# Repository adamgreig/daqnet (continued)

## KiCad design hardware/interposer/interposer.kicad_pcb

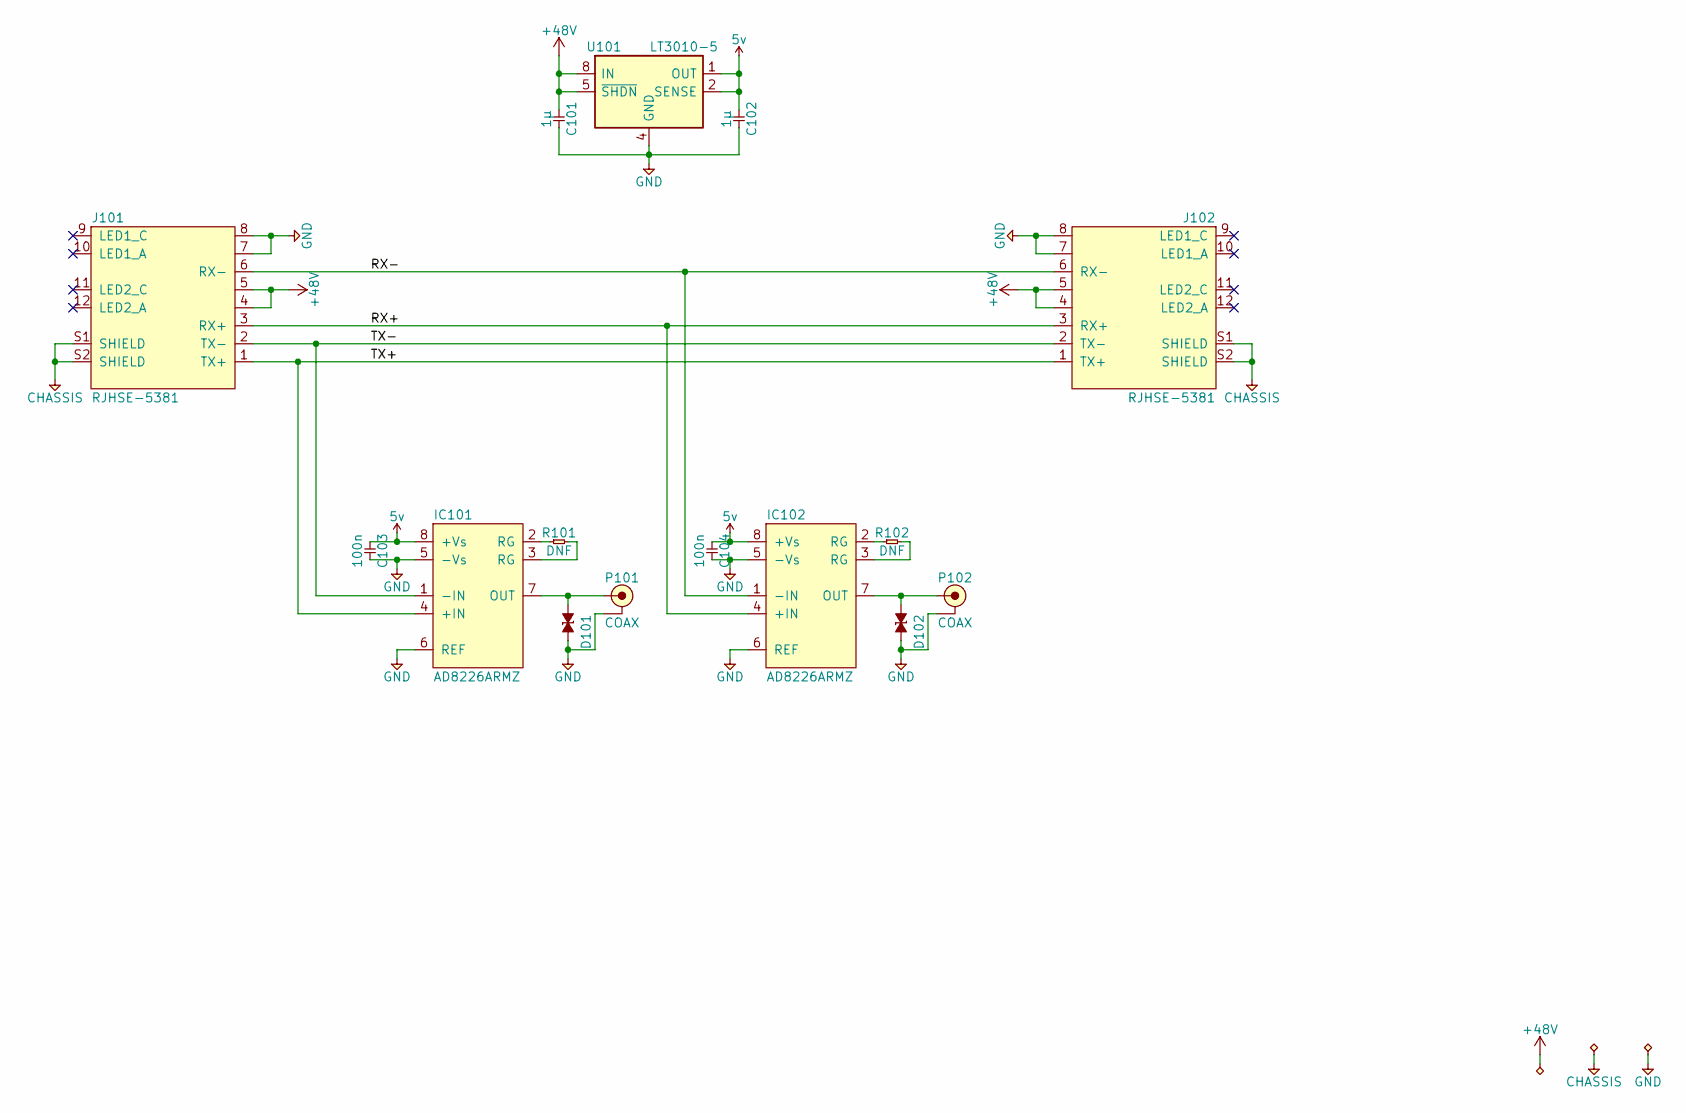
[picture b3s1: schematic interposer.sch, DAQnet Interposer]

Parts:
C101, C102: 1µ; 0805
C103, C104: 100n; 0402
D101: ESD_DIODE; 0402
D102: ESD_DIODE; 0402; Farnell 2368169
IC101, IC102: AD8226ARMZ; MSOP-8
J101, J102: RJHSE-5381; RJHSE-538X
P101, P102: COAX; SMA-EDGE
R101, R102: DNF; 0402
U101: LT3010-5; MSOP-8-1EP_3x3mm_P0.65mm_EP1.68x1.88mm

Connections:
5v: C102.1, C103.1, C104.1, IC101.8 (+Vs), IC102.8 (+Vs), U101.1 (OUT), U101.2 (SENSE)
+48V: C101.1, J101.4, J101.5, J102.4, J102.5, U101.5 (~SHDN), U101.8 (IN)
/RX+: IC102.4 (+IN), J101.3 (RX+), J102.3 (RX+)
/RX-: IC102.1 (-IN), J101.6 (RX-), J102.6 (RX-)
/TX+: IC101.4 (+IN), J101.1 (TX+), J102.1 (TX+)
/TX-: IC101.1 (-IN), J101.2 (TX-), J102.2 (TX-)
CHASSIS: J101.S1 (SHIELD), J101.S2 (SHIELD), J102.S1 (SHIELD), J102.S2 (SHIELD)
GND: C101.2, C102.2, C103.2, C104.2, D101.2, D102.2, IC101.5 (-Vs), IC101.6 (REF), IC102.5 (-Vs), IC102.6 (REF), J101.7, J101.8, J102.7, J102.8, P101.2 (GND), P102.2 (GND), U101.4 (GND), U101.9 (GND)
unnamed: D101.1, IC101.7 (OUT), P101.1 (RF)
unnamed: D102.1, IC102.7 (OUT), P102.1 (RF)
unnamed: IC101.2 (RG), R101.1
unnamed: IC101.3 (RG), R101.2
unnamed: IC102.2 (RG), R102.1
unnamed: IC102.3 (RG), R102.2

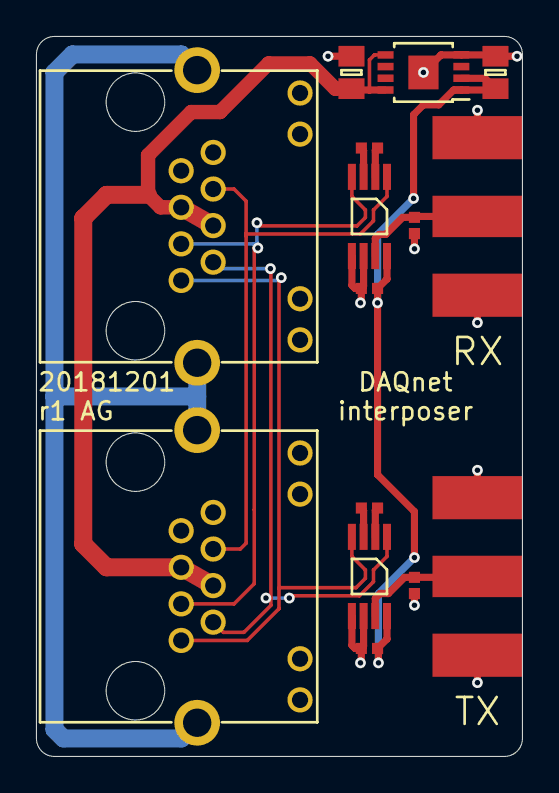
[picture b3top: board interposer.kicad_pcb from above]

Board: 2 copper layers, 27.0 x 40.0 mm, 15 parts (0 on the bottom side), 14 nets.

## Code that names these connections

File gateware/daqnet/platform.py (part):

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        ),
        Resource(
            "daqnet", 0,
            Subsignal("led1", Pins("A3", dir="o")),
            Subsignal("led2", Pins("A4", dir="o")),
            Subsignal("txp", Pins("C2", dir="o")),
            Subsignal("txn", Pins("C1", dir="o")),
            Subsignal("rx", Pins("B2", dir="i")),
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            "rmii", 0,
            Subsignal("txd0", Pins("J3", dir="o")),
            Subsignal("txd1", Pins("L1", dir="o")),
            Subsignal("txen", Pins("L2", dir="o")),
            Subsignal("rxd0", Pins("K5", dir="i")),
            Subsignal("rxd1", Pins("J5", dir="i")),
            Subsignal("crs_dv", Pins("L4", dir="i")),
            Subsignal("ref_clk", Pins("K4", dir="i")),
        ),
        Resource(
            "mdio", 0,
            Subsignal("mdc", Pins("K3", dir="o")),
            Subsignal("mdio", Pins("L3", dir="io")),
        ),
        Resource(
            "phy", 0,
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        ),
        Resource(
            "daqnet", 0,
            Subsignal("led1", Pins("C4", dir="o")),
            Subsignal("led2", Pins("D3", dir="o")),
            Subsignal("txp", Pins("B1", dir="o")),
            Subsignal("txn", Pins("B2", dir="o")),
            Subsignal("rx", Pins("C1", dir="i")),
        ),
        Resource(
            "daqnet", 1,
            Subsignal("led1", Pins("D2", dir="o")),
            Subsignal("led2", Pins("C3", dir="o")),
            Subsignal("txp", Pins("E1", dir="o")),
            Subsignal("txn", Pins("D1", dir="o")),
            Subsignal("rx", Pins("E3", dir="i")),
        ),
        Resource(
            "daqnet", 2,
            Subsignal("led1", Pins("G3", dir="o")),
            Subsignal("led2", Pins("F3", dir="o")),
            Subsignal("txp", Pins("F1", dir="o")),
            Subsignal("txn", Pins("F2", dir="o")),
            Subsignal("rx", Pins("G2", dir="i")),
        ),
        Resource(
            "daqnet", 3,
            Subsignal("led1", Pins("F4", dir="o")),
            Subsignal("led2", Pins("H3", dir="o")),
            Subsignal("txp", Pins("H1", dir="o")),
            Subsignal("txn", Pins("H2", dir="o")),
            Subsignal("rx", Pins("K1", dir="i")),
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
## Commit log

2018-11-26 initial commit. some pcb work and generic gateware.
2018-11-27 rtm proto sensor and switch
2018-11-27 rename to daqnet
2018-11-27 add protoswitch/sensor platforms
2018-11-29 fix annotations on switch; generate BOMs
2018-11-29 remove backup files
2018-12-01 add interposer
2018-12-03 add interposer bom
2018-12-03 add mdio controller
2018-12-03 add write test; randomise tests; swap rise/fall logic into clock generation; replace array with shifts
2018-12-03 swap back to using arrays as they use fewer resources
2018-12-03 rename register to reg_addr
2018-12-03 tidy up mdio
2018-12-04 Add start of MAC and add PHY controller
2018-12-05 Fix MDIO and MAC link detection
2018-12-05 tidy up mac/mdio
2018-12-06 Add first go at CRC32. Could perhaps get double throughput and need to check exactly what bit and byte order ethernet FCS really is.
2018-12-08 RMII RX working (mostly?)
2018-12-08 Reset CRC module each frame
2018-12-09 Improve RMII CDC
2018-12-09 Add MAC address matching to MAC
2018-12-10 Improve LED function
2018-12-10 Refactor mac address matching out of rmii
2018-12-10 RMII TX
2018-12-10 Add TX to MAC; add IPG to TX; demo spamming TX
2018-12-11 Working MAC TX/RX
2018-12-20 Timing technically violated but we now receive ARP reqs and send replies!
2018-12-20 Don't bother extracting destination mac addr by default (since we've already filtered on it)
2018-12-21 WIP ipv4/icmp incomplete
2019-01-04 Tidy up mac_address_match
2019-01-07 WIP nmigen port
2019-01-08 Rework platform/top to be a lot neater
2019-01-09 Refactor InstanceWrapper
2019-01-09 Start trying to think about porting ethernet stuff
2019-01-09 Port MDIO to nmigen
2019-01-10 Further porting efforts. Just weird bugs to clear up.
2019-01-10 Finish porting MAC to nmigen. IP stack still unported.
2019-01-10 Explicitly add output ports to submodules
2019-01-15 Update Platform.get_tristate for new nmigen
2019-01-15 Fix driving phy_rst properly
2019-01-15 Fix minimum mask width...
2019-01-15 rejig ports throughout nmigen design
2019-01-16 Rework MAC to use FIFOs for packet metadata in/out
2019-01-17 Progress towards new IP stack
2019-01-17 Working ARP responses albeit at 75MHz and with hardcoded tx_len/tx_offset
2019-01-17 Remove underscores from StackLayer method names
2019-01-20 Add registers between ip layers
2019-01-20 Add IPv4 and ICMPv4
2019-01-20 Add more delay to fix CDC issues a bit
2019-01-21 Swap from DummyFIFO to new nmigen AsyncFIFO
2019-01-21 Fix RMII RX test
2019-01-21 Add MIT license
2019-01-23 Combine length and offset FIFOs
2019-01-25 Update MAC/IP to parameterise tx/rx buffer size; fix rmii tx padding checksum bug
2019-01-27 Update for latest nmigen
2019-01-31 Add UDP send/receive via user BRAM
2019-02-04 Make IPChecksum take an explicit byte position input
2019-02-04 Remove opt-timing for use with analytical placer in nextpnr
2019-02-04 Add random udp scripts
2019-05-24 Update to latest nmigen master
    Combines changes from #1 with other required fixes for latest nmigen and
    yosys, including changes to inference for transparent memory in iCE40.
2019-06-13 Update for latest nmigen; use nmigen built-in iCE40 platform
2019-06-14 Use seed arg, set nextpnr freq, set yosys relut
2019-07-09 fix test failure
2019-07-09 add simple pipelined adder
2020-07-21 Fix _InstanceWrapper
